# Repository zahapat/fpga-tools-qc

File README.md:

# CDL FPGA Environment for Quantum Computing

Welcome to the FPGA Environment for Quantum Computing template repository.

This repository is primarily designed for use with the [Xilinx Vivado Design Suite (HLx Edition build 2020.2)](https://www.xilinx.com/support/download/index.html/content/xilinx/en/downloadNav/vivado-design-tools/archive.html) on Windows platforms.

This repository contains VLSI hardware components, PCB layouts for Opal Kelly boards, and Vivado board files for high-speed data acquisition, clock synthesis, and other purposes within a quantum laboratory.

## Prerequisites

1. [Vivado Design Suite (HLx Edition build 2020.2)](https://www.xilinx.com/support/download/index.html/content/xilinx/en/downloadNav/vivado-design-tools/archive.html)
2. [ModelSim-Intel® FPGA Standard Edition, Version 20.1std](https://www.intel.com/content/www/us/en/software-kit/750637/modelsim-intel-fpgas-standard-edition-software-version-20-1.html?)
3. [Cygwin](https://www.cygwin.com/install.html) (GNU and Open Source tools for Linux-like functionality on Windows)
4. [App Installer (Winget)](https://apps.microsoft.com/store/detail/app-installer/9NBLGGH4NNS1) available on Microsoft Store.
5. Run all scripts in the directory `'./scripts/installers/win11/'` in the order 1 to 6 (plus the optional batch script afterwise) as an administrator to configure environment variables, install chocolate, Microsoft PowerShell, GitHub CLI (gh), and Make.
6. If you do not wish to install Python, comment the nineth line in the `'RunAsAdmin2-InstallEssentialAppsWin11.bat'`
7. After installing all the required software, go to the directory of this environment. Open this directory in your favourite terminal and run:
    ```shell
    make sim_init
    ```
    This will create a modelsim.ini file in the environment's root directory, necessary to launch simulations.

## Desctiption

The tools provided with this repository serve to offer tools and VLSI source files for facilitating the development of FPGA-based projects to build optimal and resource-efficient hardware.

One can find the following subdirectories:

1. Tcl

    `./tcl` contains Tcl scripts that interact with software supporting a Tcl (Tickle) console. They are designed for automating project building and running simulations using CLI (command-line interface).

2. Scripts

    The `'./scripts'` directory consists of the following tools:

   - Python-Notebook-Based FQEnv wrapper and control tool
   - The search for optimal MMCM (Mixed Mode Clock Manager) primitives analyzer for optimal clock synthesis
   - FIR Coefficients Generator
   - Generic parameters generator
   - Data Visualizer after successful readout

3. Modules

    The `./modules` directory serves as a repository of HDL modules created throughout the development. These modules consist of hardware description and Tcl scripts for adding files to Vivado Design Suite and Modelsim in correct compile order.

4. Boards

    This directory serves as a repository of Tcl-based generators of Vivado board `'*.bd'` files necessary to integrate the project cores with various AXI-based components. It is possible to inspect such bd file in Vivado IDE.

5. PCB

    The `'./pcb'` directory contains PCB design source files and gerber files to view, review, modify, or adapt PCB designs to new designs using KiCad. Gerber files can be directly sent to a PCB manufacturer.

6. Do

    The `'./do'` directory contains do scripts that enable launching and compiling source files within ModelSim.

7. Simulator

    The `'./simulator'` directory accompanies scripts in the `./do` directory. This is the output directory of the ModelSim simualtor. Also, it contains other basic do scripts to control simulation via the ModelSim Tcl command-line. Do scripts can be programmed using Tcl language.

8. Vivado

    This folder contains the Vivado project. While building the project, report files are being generated to inspect the properties of the hardware being generated, its resource utilization, timing, and more. These properties can also be inspected after launching the `*.xpr` Vivado project file located in this directory.

## Basic Functionality

The core unit of the FPGA Environment is the central Makefile located in the root direcotry of this repository. When opened in a text editor, it consists variables in upprecase and make targets which are named based on what one intends to do. For example, the `'make src'` target will add sources to Vivado; and `'make board'` will create and add the bd file to vivado. 

The following example reflects the main implementation flow. Run the following commands in your terminal after navigating to the root directory.

- Reset the environment:
    ```shell
    make reset
    ```

- Add all HDL sources under the given the relative Top file located in modules directory. In this case, the TOP variable defined in the Makefile will be explicitly updated by the desired source:
    ```shell
    make src TOP=fsm_gflow_tb.vhd
    ```

- To launch the simulation, type the following to the command line while being in the project root directory. This will launch ModelSim and start the simulation:
    ```shell
    make sim_gui
    ```

- To run hardware synthesis in out-of-context mode, run the following command:
    ```shell
    make ooc TOP=TOP=fsm_gflow.vhd
    ```

- To view the results in Vivado GUI mode, type the following to the CLI and wait until the project is open in Vivado:
    ```shell
    make gui
    ```

- Run all stages of implementation: synthesis, implementation, bitstream generation, hw platform generation (if applicable)
    ```shell
    make all
    ```

## Git: Create a New Repository

Update the `GIT_EMAIL` variable in `git.mk`. Use your email address to link Git with your Git account.
Run the following command to create a new private repo:

```shell
$ make git_new_private_repo
```

Run the following command to create a new public repository:

```shell
$ make git_new_public_repo
```

Run the following command to make the repository as a template:

```shell
$ make git_make_this_repo_template
```

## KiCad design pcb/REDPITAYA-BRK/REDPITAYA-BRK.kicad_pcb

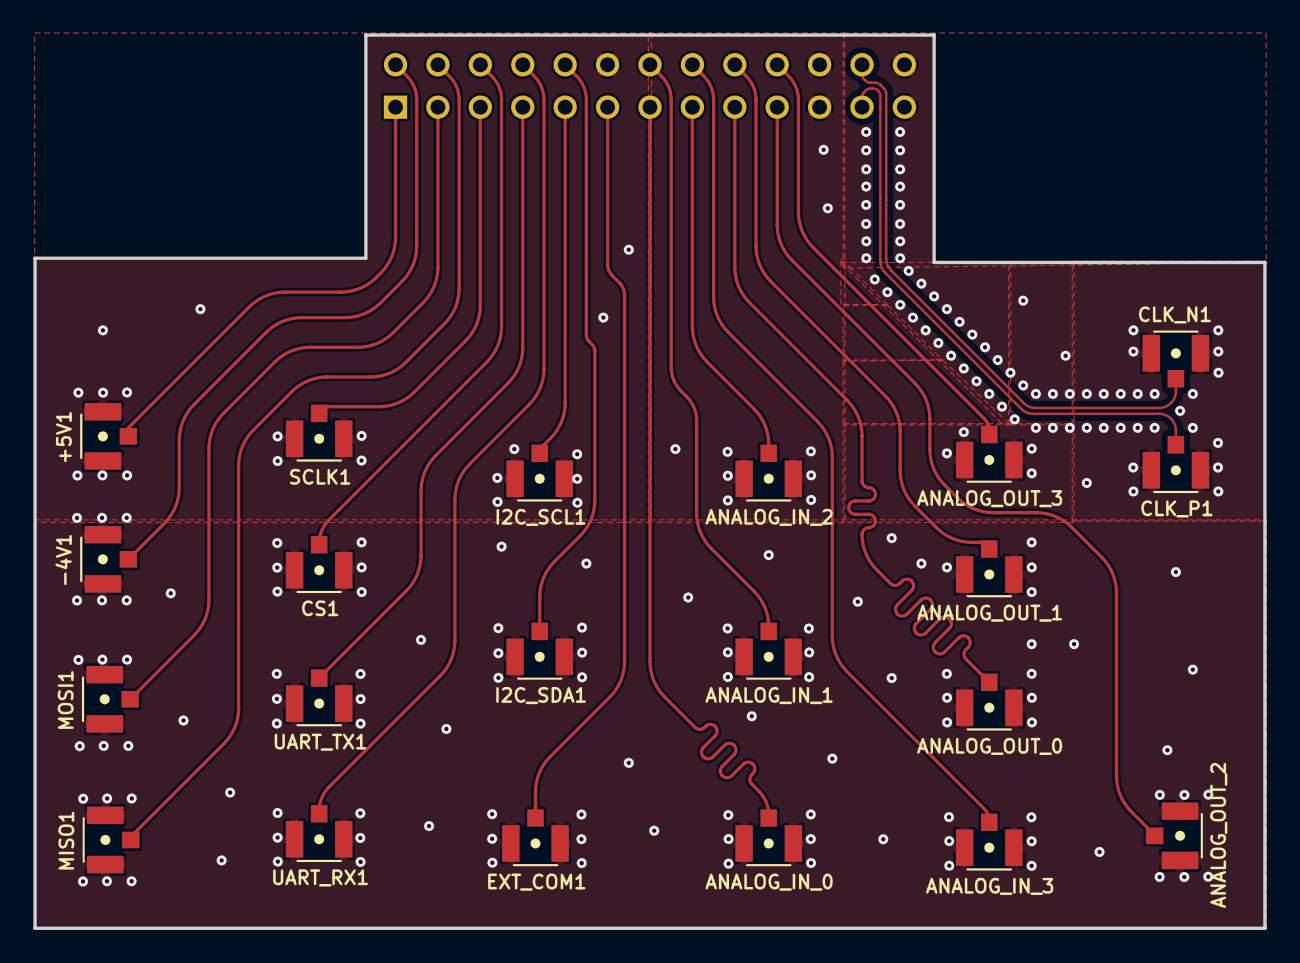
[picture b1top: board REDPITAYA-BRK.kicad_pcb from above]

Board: 4 copper layers, 73.7 x 53.5 mm, 22 parts (1 on the bottom side), 22 nets.

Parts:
+5V1: U.FL-R-SMT-1(10); HRS_U.FL-R-SMT-1(10)
-4V1: U.FL-R-SMT-1(10); HRS_U.FL-R-SMT-1(10)
ANALOG_IN_0, ANALOG_IN_1, ANALOG_IN_2, ANALOG_IN_3: U.FL-R-SMT-1(10); HRS_U.FL-R-SMT-1(10)
ANALOG_OUT_0, ANALOG_OUT_1, ANALOG_OUT_2, ANALOG_OUT_3: U.FL-R-SMT-1(10); HRS_U.FL-R-SMT-1(10)
CLK_N1: U.FL-R-SMT-1(10); HRS_U.FL-R-SMT-1(10)
CLK_P1: U.FL-R-SMT-1(10); HRS_U.FL-R-SMT-1(10)
CS1: U.FL-R-SMT-1(10); HRS_U.FL-R-SMT-1(10)
EXT_COM1: U.FL-R-SMT-1(10); HRS_U.FL-R-SMT-1(10)
I2C_SCL1, I2C_SDA1: U.FL-R-SMT-1(10); HRS_U.FL-R-SMT-1(10)
J1: 6-534206-3; TE_6-534206-3
MISO1: U.FL-R-SMT-1(10); HRS_U.FL-R-SMT-1(10)
MOSI1: U.FL-R-SMT-1(10); HRS_U.FL-R-SMT-1(10)
SCLK1: U.FL-R-SMT-1(10); HRS_U.FL-R-SMT-1(10)
UART_RX1: U.FL-R-SMT-1(10); HRS_U.FL-R-SMT-1(10)
UART_TX1: U.FL-R-SMT-1(10); HRS_U.FL-R-SMT-1(10)

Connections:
/CLK_N: CLK_N1.2 (SIG), J1.25
/CLK_P: CLK_P1.2 (SIG), J1.12
/ai0: ANALOG_IN_0.2 (SIG), J1.7
/ai1: ANALOG_IN_1.2 (SIG), J1.20
/ai2: ANALOG_IN_2.2 (SIG), J1.8
/ai3: ANALOG_IN_3.2 (SIG), J1.21
/ao0: ANALOG_OUT_0.2 (SIG), J1.9
/ao1: ANALOG_OUT_1.2 (SIG), J1.22
/ao2: ANALOG_OUT_2.2 (SIG), J1.10
/ao3: ANALOG_OUT_3.2 (SIG), J1.23
/cs: CS1.2 (SIG), J1.16
/ext_com: EXT_COM1.2 (SIG), J1.6
/i2c_scl: I2C_SCL1.2 (SIG), J1.5
/i2c_sda: I2C_SDA1.2 (SIG), J1.18
/m4v: -4V1.2 (SIG), J1.14
/miso: J1.15, MISO1.2 (SIG)
/mosi: J1.2, MOSI1.2 (SIG)
/p5v: +5V1.2 (SIG), J1.1
/sclk: J1.3, SCLK1.2 (SIG)
/uart_rx: J1.17, UART_RX1.2 (SIG)
/uart_tx: J1.4, UART_TX1.2 (SIG)
GND: +5V1.1 (GND), +5V1.3 (GND), -4V1.1 (GND), -4V1.3 (GND), ANALOG_IN_0.1 (GND), ANALOG_IN_0.3 (GND), ANALOG_IN_1.1 (GND), ANALOG_IN_1.3 (GND), ANALOG_IN_2.1 (GND), ANALOG_IN_2.3 (GND), ANALOG_IN_3.1 (GND), ANALOG_IN_3.3 (GND), ANALOG_OUT_0.1 (GND), ANALOG_OUT_0.3 (GND), ANALOG_OUT_1.1 (GND), ANALOG_OUT_1.3 (GND), ANALOG_OUT_2.1 (GND), ANALOG_OUT_2.3 (GND), ANALOG_OUT_3.1 (GND), ANALOG_OUT_3.3 (GND), CLK_N1.1 (GND), CLK_N1.3 (GND), CLK_P1.1 (GND), CLK_P1.3 (GND), CS1.1 (GND), CS1.3 (GND), EXT_COM1.1 (GND), EXT_COM1.3 (GND), I2C_SCL1.1 (GND), I2C_SCL1.3 (GND), I2C_SDA1.1 (GND), I2C_SDA1.3 (GND), J1.11, J1.13, J1.19, J1.24, J1.26, MISO1.1 (GND), MISO1.3 (GND), MOSI1.1 (GND), MOSI1.3 (GND), SCLK1.1 (GND), SCLK1.3 (GND), UART_RX1.1 (GND), UART_RX1.3 (GND), UART_TX1.1 (GND), UART_TX1.3 (GND)

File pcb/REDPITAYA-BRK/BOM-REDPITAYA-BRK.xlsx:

|  |  | xxxx xxxx xxxxx xxPCS BOM (Sample Bill of Materials)
Item # | *Designator | *Qty | Manufacturer | *Mfg Part # | Description / Value | *Package/Footprint | Type | Your Instructions / Notes
1 | ANALOG_OUT_1 | 1 | Hirose Electric Co Ltd | U.FL-R-SMT-1(10) | U.FL (UMCC) Connector Receptacle, Male Pin 50Ohm Surface Mount Solder | HRS_U.FL-R-SMT-1(10) | SMD | Datasheet: https://media.digikey.com/pdf/Data%20Sheets/Hirose%20PDFs/ED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
2 | +5V1 | 1 | Hirose Electric Co Ltd | U.FL-R-SMT-1(10) | U.FL (UMCC) Connector Receptacle, Male Pin 50Ohm Surface Mount Solder | HRS_U.FL-R-SMT-1(10) | SMD | Datasheet: https://media.digikey.com/pdf/Data%20Sheets/Hirose%20PDFs/ED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
3 | I2C_SDA1 | 1 | Hirose Electric Co Ltd | U.FL-R-SMT-1(10) | U.FL (UMCC) Connector Receptacle, Male Pin 50Ohm Surface Mount Solder | HRS_U.FL-R-SMT-1(10) | SMD | Datasheet: https://media.digikey.com/pdf/Data%20Sheets/Hirose%20PDFs/ED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
4 | ANALOG_IN_3 | 1 | Hirose Electric Co Ltd | U.FL-R-SMT-1(10) | U.FL (UMCC) Connector Receptacle, Male Pin 50Ohm Surface Mount Solder | HRS_U.FL-R-SMT-1(10) | SMD | Datasheet: https://media.digikey.com/pdf/Data%20Sheets/Hirose%20PDFs/ED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
5 | -4V1 | 1 | Hirose Electric Co Ltd | U.FL-R-SMT-1(10) | U.FL (UMCC) Connector Receptacle, Male Pin 50Ohm Surface Mount Solder | HRS_U.FL-R-SMT-1(10) | SMD | Datasheet: https://media.digikey.com/pdf/Data%20Sheets/Hirose%20PDFs/ED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
6 | UART_RX1 | 1 | Hirose Electric Co Ltd | U.FL-R-SMT-1(10) | U.FL (UMCC) Connector Receptacle, Male Pin 50Ohm Surface Mount Solder | HRS_U.FL-R-SMT-1(10) | SMD | Datasheet: https://media.digikey.com/pdf/Data%20Sheets/Hirose%20PDFs/ED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
7 | ANALOG_IN_0 | 1 | Hirose Electric Co Ltd | U.FL-R-SMT-1(10) | U.FL (UMCC) Connector Receptacle, Male Pin 50Ohm Surface Mount Solder | HRS_U.FL-R-SMT-1(10) | SMD | Datasheet: https://media.digikey.com/pdf/Data%20Sheets/Hirose%20PDFs/ED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
8 | UART_TX1 | 1 | Hirose Electric Co Ltd | U.FL-R-SMT-1(10) | U.FL (UMCC) Connector Receptacle, Male Pin 50Ohm Surface Mount Solder | HRS_U.FL-R-SMT-1(10) | SMD | Datasheet: https://media.digikey.com/pdf/Data%20Sheets/Hirose%20PDFs/ED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
9 | EXT_COM1 | 1 | Hirose Electric Co Ltd | U.FL-R-SMT-1(10) | U.FL (UMCC) Connector Receptacle, Male Pin 50Ohm Surface Mount Solder | HRS_U.FL-R-SMT-1(10) | SMD | Datasheet: https://media.digikey.com/pdf/Data%20Sheets/Hirose%20PDFs/ED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
10 | MOSI1 | 1 | Hirose Electric Co Ltd | U.FL-R-SMT-1(10) | U.FL (UMCC) Connector Receptacle, Male Pin 50Ohm Surface Mount Solder | HRS_U.FL-R-SMT-1(10) | SMD | Datasheet: https://media.digikey.com/pdf/Data%20Sheets/Hirose%20PDFs/ED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
11 | ANALOG_IN_1 | 1 | Hirose Electric Co Ltd | U.FL-R-SMT-1(10) | U.FL (UMCC) Connector Receptacle, Male Pin 50Ohm Surface Mount Solder | HRS_U.FL-R-SMT-1(10) | SMD | Datasheet: https://media.digikey.com/pdf/Data%20Sheets/Hirose%20PDFs/ED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
12 | ANALOG_IN_2 | 1 | Hirose Electric Co Ltd | U.FL-R-SMT-1(10) | U.FL (UMCC) Connector Receptacle, Male Pin 50Ohm Surface Mount Solder | HRS_U.FL-R-SMT-1(10) | SMD | Datasheet: https://media.digikey.com/pdf/Data%20Sheets/Hirose%20PDFs/ED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
13 | CLK_N1 | 1 | Hirose Electric Co Ltd | U.FL-R-SMT-1(10) | U.FL (UMCC) Connector Receptacle, Male Pin 50Ohm Surface Mount Solder | HRS_U.FL-R-SMT-1(10) | SMD | Datasheet: https://media.digikey.com/pdf/Data%20Sheets/Hirose%20PDFs/ED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
14 | ANALOG_OUT_2 | 1 | Hirose Electric Co Ltd | U.FL-R-SMT-1(10) | U.FL (UMCC) Connector Receptacle, Male Pin 50Ohm Surface Mount Solder | HRS_U.FL-R-SMT-1(10) | SMD | Datasheet: https://media.digikey.com/pdf/Data%20Sheets/Hirose%20PDFs/ED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
15 | ANALOG_OUT_0 | 1 | Hirose Electric Co Ltd | U.FL-R-SMT-1(10) | U.FL (UMCC) Connector Receptacle, Male Pin 50Ohm Surface Mount Solder | HRS_U.FL-R-SMT-1(10) | SMD | Datasheet: https://media.digikey.com/pdf/Data%20Sheets/Hirose%20PDFs/ED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
16 | MISO1 | 1 | Hirose Electric Co Ltd | U.FL-R-SMT-1(10) | U.FL (UMCC) Connector Receptacle, Male Pin 50Ohm Surface Mount Solder | HRS_U.FL-R-SMT-1(10) | SMD | Datasheet: https://media.digikey.com/pdf/Data%20Sheets/Hirose%20PDFs/ED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
17 | ANALOG_OUT_3 | 1 | Hirose Electric Co Ltd | U.FL-R-SMT-1(10) | U.FL (UMCC) Connector Receptacle, Male Pin 50Ohm Surface Mount Solder | HRS_U.FL-R-SMT-1(10) | SMD | Datasheet: https://media.digikey.com/pdf/Data%20Sheets/Hirose%20PDFs/ED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
18 | CLK_P1 | 1 | Hirose Electric Co Ltd | U.FL-R-SMT-1(10) | U.FL (UMCC) Connector Receptacle, Male Pin 50Ohm Surface Mount Solder | HRS_U.FL-R-SMT-1(10) | SMD | Datasheet: https://media.digikey.com/pdf/Data%20Sheets/Hirose%20PDFs/ED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
19 | SCLK1 | 1 | Hirose Electric Co Ltd | U.FL-R-SMT-1(10) | U.FL (UMCC) Connector Receptacle, Male Pin 50Ohm Surface Mount Solder | HRS_U.FL-R-SMT-1(10) | SMD | Datasheet: https://media.digikey.com/pdf/Data%20Sheets/Hirose%20PDFs/ED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
20 | I2C_SCL1 | 1 | Hirose Electric Co Ltd | U.FL-R-SMT-1(10) | U.FL (UMCC) Connector Receptacle, Male Pin 50Ohm Surface Mount Solder | HRS_U.FL-R-SMT-1(10) | SMD | Datasheet: https://media.digikey.com/pdf/Data%20Sheets/Hirose%20PDFs/ED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
21 | CS1 | 1 | Hirose Electric Co Ltd | U.FL-R-SMT-1(10) | U.FL (UMCC) Connector Receptacle, Male Pin 50Ohm Surface Mount Solder | HRS_U.FL-R-SMT-1(10) | SMD | Datasheet: https://media.digikey.com/pdf/Data%20Sheets/Hirose%20PDFs/ED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
22 | J1 | 1 | TE Connectivity AMP Connectors | 6-534206-3 | 26 Position Receptacle Connector 0.100" (2.54mm) Through Hole Gold | TE_6-534206-3 | SMD | Datasheet: https://www.te.com/commerce/DocumentDelivery/DDEController?A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

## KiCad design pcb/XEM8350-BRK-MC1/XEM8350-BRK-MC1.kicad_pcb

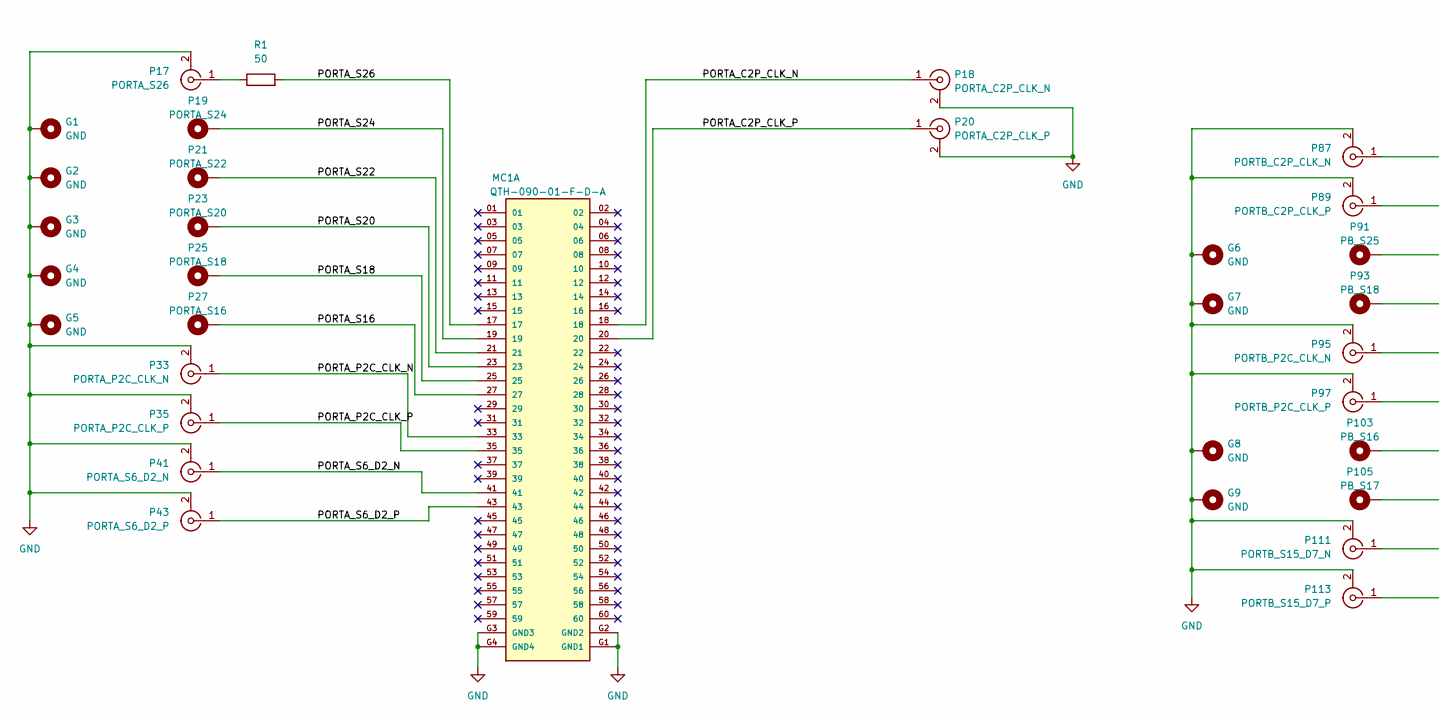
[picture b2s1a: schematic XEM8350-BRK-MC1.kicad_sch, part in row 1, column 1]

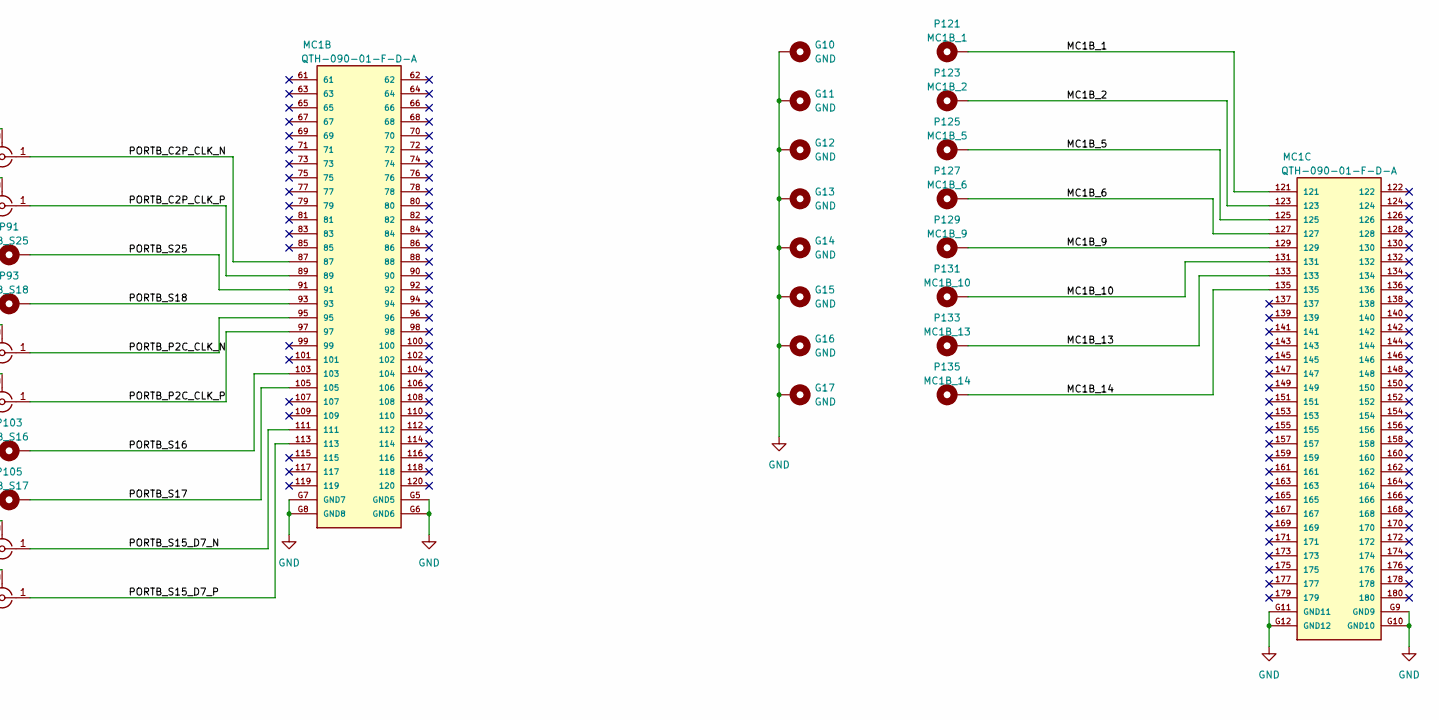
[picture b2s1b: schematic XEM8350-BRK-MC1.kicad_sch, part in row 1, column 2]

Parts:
G1, G2, G3, G4, G5, G6, G7, G8, G9, G10, G11, G12, G13, G14, G15, G16, G17: GND; Custom_Signal_Hole_Pad-001
MC1: QTH-090-01-F-D-A; SAMTEC_QTH-090-01-X-D-A; PARTREV L
P17: PORTA_S26; SMA_Amphenol_901-144_Vertical
P18: PORTA_C2P_CLK_N; SMA_Amphenol_901-144_Vertical
P19: PORTA_S24; Custom_Signal_Hole_Pad-001
P20: PORTA_C2P_CLK_P; SMA_Amphenol_901-144_Vertical
P21: PORTA_S22; Custom_Signal_Hole_Pad-001
P23: PORTA_S20; Custom_Signal_Hole_Pad-001
P25: PORTA_S18; Custom_Signal_Hole_Pad-001
P27: PORTA_S16; Custom_Signal_Hole_Pad-001
P33: PORTA_P2C_CLK_N; SMA_Amphenol_901-144_Vertical
P35: PORTA_P2C_CLK_P; SMA_Amphenol_901-144_Vertical
P41: PORTA_S6_D2_N; SMA_Amphenol_901-144_Vertical
P43: PORTA_S6_D2_P; SMA_Amphenol_901-144_Vertical
P87: PORTB_C2P_CLK_N; SMA_Amphenol_901-144_Vertical
P89: PORTB_C2P_CLK_P; SMA_Amphenol_901-144_Vertical
P91: PB_S25; Custom_Signal_Hole_Pad-001
P93: PB_S18; Custom_Signal_Hole_Pad-001
P95: PORTB_P2C_CLK_N; SMA_Amphenol_901-144_Vertical
P97: PORTB_P2C_CLK_P; SMA_Amphenol_901-144_Vertical
P103: PB_S16; Custom_Signal_Hole_Pad-001
P105: PB_S17; Custom_Signal_Hole_Pad-001
P111: PORTB_S15_D7_N; SMA_Amphenol_901-144_Vertical
P113: PORTB_S15_D7_P; SMA_Amphenol_901-144_Vertical
P121: MC1B_1; Custom_Signal_Hole_Pad-001
P123: MC1B_2; Custom_Signal_Hole_Pad-001
P125: MC1B_5; Custom_Signal_Hole_Pad-001
P127: MC1B_6; Custom_Signal_Hole_Pad-001
P129: MC1B_9; Custom_Signal_Hole_Pad-001
P131: MC1B_10; Custom_Signal_Hole_Pad-001
P133: MC1B_13; Custom_Signal_Hole_Pad-001
P135: MC1B_14; Custom_Signal_Hole_Pad-001
R1: 50; RESC1608X59N

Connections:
/MC1B_1: MC1.121, P121.1
/MC1B_2: MC1.123, P123.1
/MC1B_5: MC1.125, P125.1
/MC1B_6: MC1.127, P127.1
/MC1B_9: MC1.129, P129.1
/MC1B_10: MC1.131, P131.1
/MC1B_13: MC1.133, P133.1
/MC1B_14: MC1.135, P135.1
/PORTA_C2P_CLK_N: MC1.18, P18.1 (In)
/PORTA_C2P_CLK_P: MC1.20, P20.1 (In)
/PORTA_P2C_CLK_N: MC1.33, P33.1 (In)
/PORTA_P2C_CLK_P: MC1.35, P35.1 (In)
/PORTA_S6_D2_N: MC1.41, P41.1 (In)
/PORTA_S6_D2_P: MC1.43, P43.1 (In)
/PORTA_S16: MC1.27, P27.1
/PORTA_S18: MC1.25, P25.1
/PORTA_S20: MC1.23, P23.1
/PORTA_S22: MC1.21, P21.1
/PORTA_S24: MC1.19, P19.1
/PORTA_S26: MC1.17, R1.2
/PORTB_C2P_CLK_N: MC1.87, P87.1 (In)
/PORTB_C2P_CLK_P: MC1.89, P89.1 (In)
/PORTB_P2C_CLK_N: MC1.95, P95.1 (In)
/PORTB_P2C_CLK_P: MC1.97, P97.1 (In)
/PORTB_S15_D7_N: MC1.111, P111.1 (In)
/PORTB_S15_D7_P: MC1.113, P113.1 (In)
/PORTB_S16: MC1.103, P103.1
/PORTB_S17: MC1.105, P105.1
/PORTB_S18: MC1.93, P93.1
/PORTB_S25: MC1.91, P91.1
GND: G1.1, G2.1, G3.1, G4.1, G5.1, G6.1, G7.1, G8.1, G9.1, G10.1, G11.1, G12.1, G13.1, G14.1, G15.1, G16.1, G17.1, MC1.G1 (GND1), MC1.G2 (GND2), MC1.G3 (GND3), MC1.G4 (GND4), MC1.G5 (GND5), MC1.G6 (GND6), MC1.G7 (GND7), MC1.G8 (GND8), MC1.G9 (GND9), MC1.G10 (GND10), MC1.G11 (GND11), MC1.G12 (GND12), P17.2 (Ext), P18.2 (Ext), P20.2 (Ext), P33.2 (Ext), P35.2 (Ext), P41.2 (Ext), P43.2 (Ext), P87.2 (Ext), P89.2 (Ext), P95.2 (Ext), P97.2 (Ext), P111.2 (Ext), P113.2 (Ext)
unnamed: P17.1 (In), R1.1

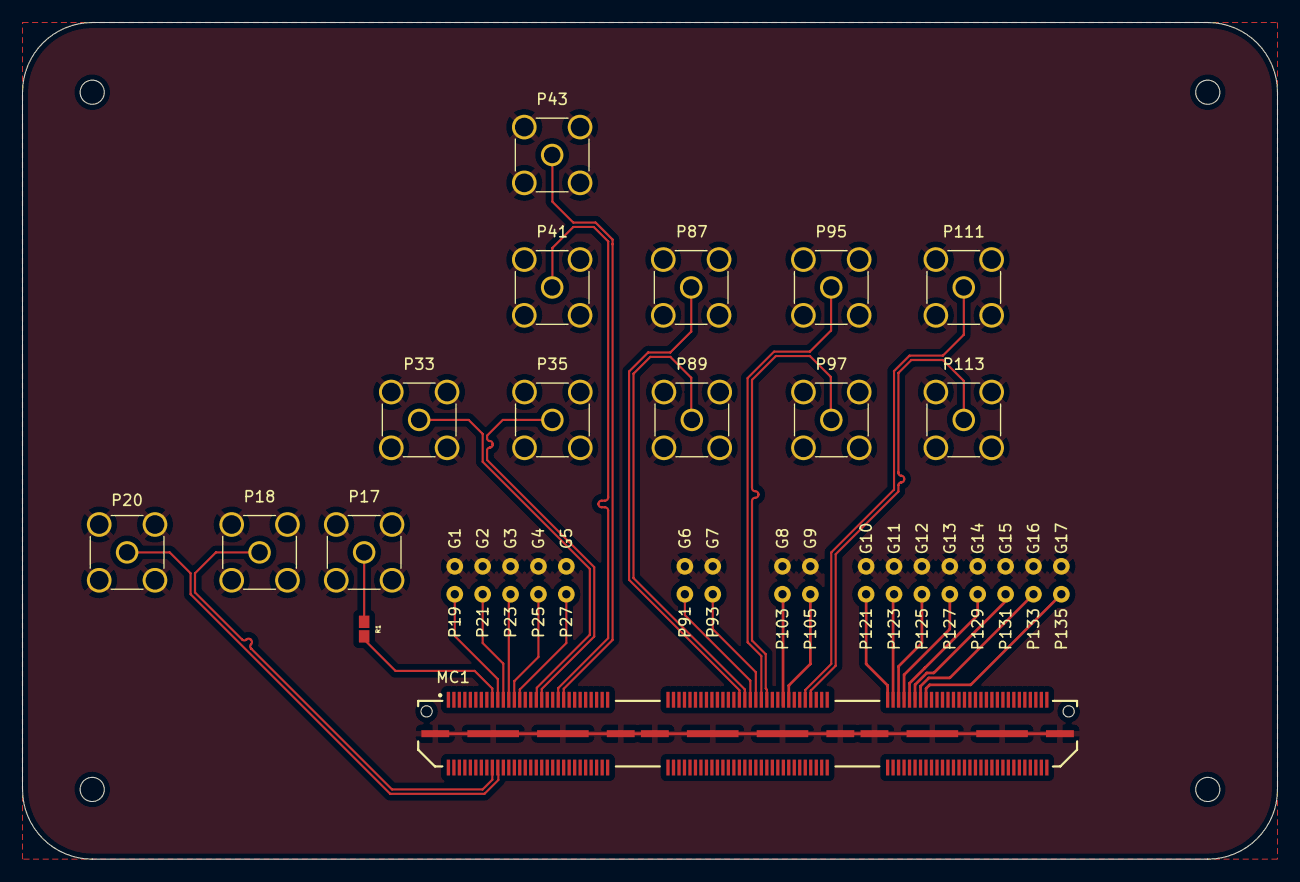
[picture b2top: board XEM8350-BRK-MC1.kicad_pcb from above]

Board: 2 copper layers, 114.3 x 76.2 mm, 49 parts (0 on the bottom side), 32 nets.

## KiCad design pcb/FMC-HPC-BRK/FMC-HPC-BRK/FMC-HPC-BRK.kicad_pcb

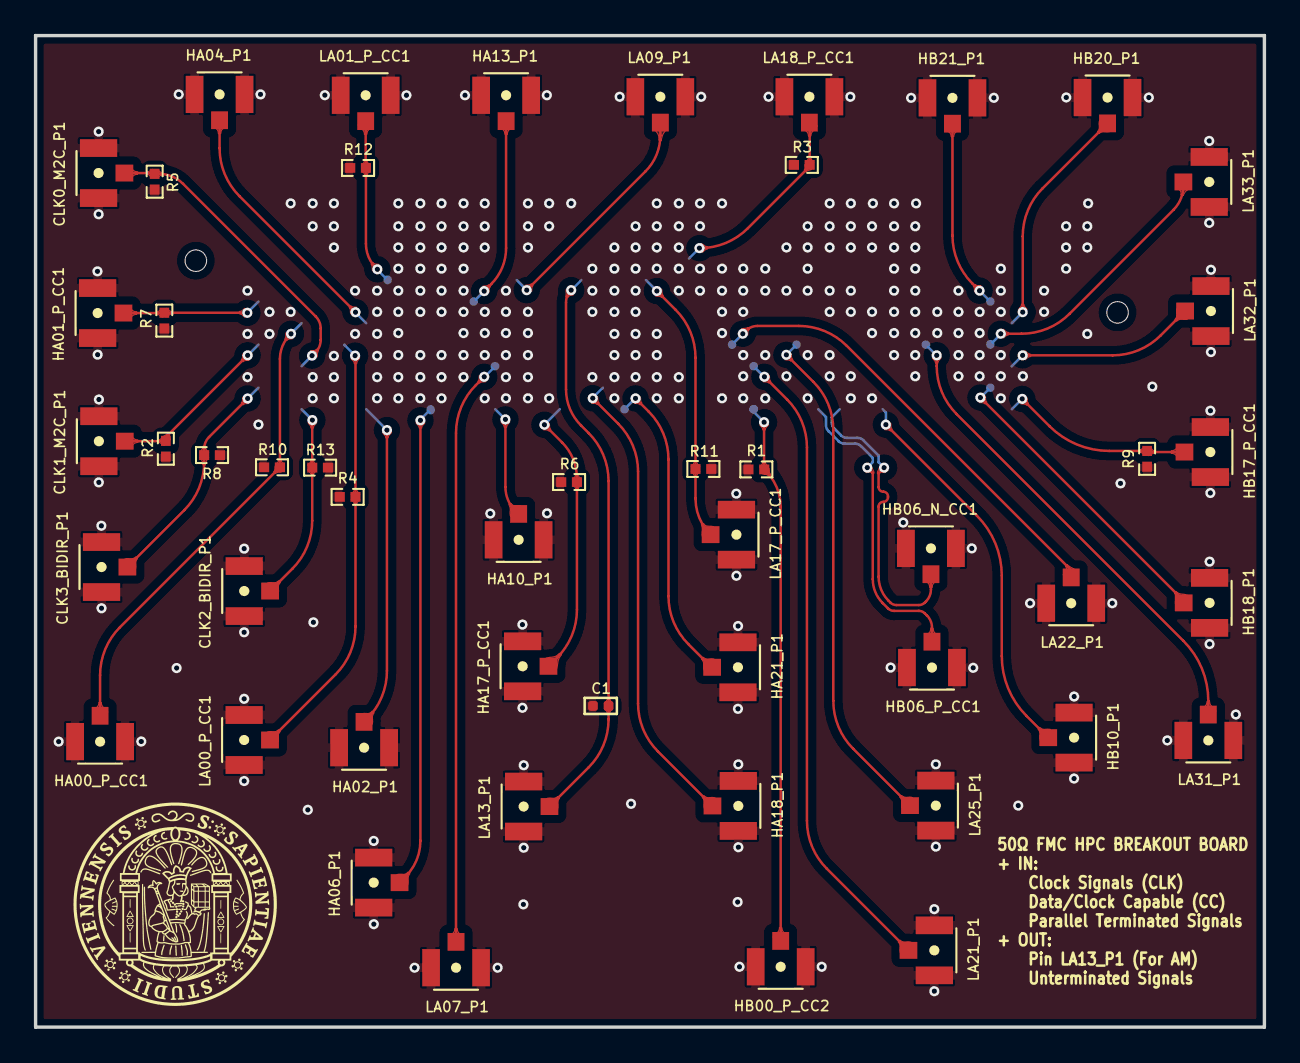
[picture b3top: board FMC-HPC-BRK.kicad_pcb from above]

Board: 4 copper layers, 72.5 x 58.5 mm, 50 parts (1 on the bottom side), 36 nets.

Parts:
C1: CAP; CAPC100X50X55L25N
CLK0_M2C_P1, CLK1_M2C_P1, CLK2_BIDIR_P1, CLK3_BIDIR_P1: U.FL-R-SMT-1(10); HRS_U.FL-R-SMT-1(10)
HA00_P_CC1, HA01_P_CC1, HA02_P1, HA04_P1, HA06_P1, HA10_P1, HA13_P1, HA17_P_CC1, HA18_P1, HA21_P1: U.FL-R-SMT-1(10); HRS_U.FL-R-SMT-1(10)
HB00_P_CC2, HB06_N_CC1, HB06_P_CC1, HB10_P1, HB17_P_CC1, HB18_P1, HB20_P1, HB21_P1: U.FL-R-SMT-1(10); HRS_U.FL-R-SMT-1(10)
J1: ASP-134488-01; SAMTEC_ASP-134488-01
LA00_P_CC1, LA01_P_CC1, LA07_P1, LA09_P1, LA13_P1, LA17_P_CC1, LA18_P_CC1, LA21_P1, LA22_P1, LA25_P1, LA31_P1, LA32_P1, LA33_P1: U.FL-R-SMT-1(10); HRS_U.FL-R-SMT-1(10)
R1, R2, R3, R4, R5, R6, R7, R8, R9, R10, R11, R12, R13: R; RESC100X50X35L25

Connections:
/B8b: J1.G33, LA01_P_CC1.2 (SIG), R12.2
/B14b: J1.G27, LA09_P1.2 (SIG)
/B17b: C1.2, J1.G24, LA13_P1.2 (SIG)
/B20b: J1.G21, LA17_P_CC1.2 (SIG), R11.2
/B22a: J1.H19, LA18_P_CC1.2 (SIG), R3.2
/C2a: HA01_P_CC1.2 (SIG), J1.F39, R7.2
/C4b: HA00_P_CC1.2 (SIG), J1.E37, R10.2
/C7b: HA04_P1.2 (SIG), J1.E34
/C12a: HA13_P1.2 (SIG), J1.F29
/C36a: HB21_P1.2 (SIG), J1.F5
/C37b: HB20_P1.2 (SIG), J1.E4
/D2a: CLK1_M2C_P1.2 (SIG), J1.D39, R2.2
/D4b: CLK0_M2C_P1.2 (SIG), J1.C37, R5.2
/D6a: J1.D35, LA00_P_CC1.2 (SIG), R4.2
/D13b: J1.C28, LA07_P1.2 (SIG)
/D24a: J1.D17, LA22_P1.2 (SIG)
/D25b: J1.C16, LA21_P1.2 (SIG)
/D27a: J1.D14, LA25_P1.2 (SIG)
/D33a: J1.D8, LA31_P1.2 (SIG)
/D36a: J1.D5, LA33_P1.2 (SIG)
/D37b: J1.C4, LA32_P1.2 (SIG)
/E2a: CLK3_BIDIR_P1.2 (SIG), J1.B39, R8.2
/E4b: CLK2_BIDIR_P1.2 (SIG), J1.A37, R13.2
/E7b: HA02_P1.2 (SIG), J1.A34
/E10b: HA06_P1.2 (SIG), J1.A31
/E13b: HA10_P1.2 (SIG), J1.A28
/E16b: HA17_P_CC1.2 (SIG), J1.A25, R6.2
/E18a: HA18_P1.2 (SIG), J1.B23
/E19b: HA21_P1.2 (SIG), J1.A22
/E25b: HB00_P_CC2.2 (SIG), J1.A16, R1.2
/E28b_N: HB06_N_CC1.2 (SIG), J1.A12
/E28b_P: HB06_P_CC1.2 (SIG), J1.A13
/E31b_P: HB10_P1.2 (SIG), J1.A10
/E36a: HB18_P1.2 (SIG), J1.B5
/E37b: HB17_P_CC1.2 (SIG), J1.A4, R9.2
GND: C1.1, CLK0_M2C_P1.1 (GND), CLK0_M2C_P1.3 (GND), CLK1_M2C_P1.1 (GND), CLK1_M2C_P1.3 (GND), CLK2_BIDIR_P1.1 (GND), CLK2_BIDIR_P1.3 (GND), CLK3_BIDIR_P1.1 (GND), CLK3_BIDIR_P1.3 (GND), HA00_P_CC1.1 (GND), HA00_P_CC1.3 (GND), HA01_P_CC1.1 (GND), HA01_P_CC1.3 (GND), HA02_P1.1 (GND), HA02_P1.3 (GND), HA04_P1.1 (GND), HA04_P1.3 (GND), HA06_P1.1 (GND), HA06_P1.3 (GND), HA10_P1.1 (GND), HA10_P1.3 (GND), HA13_P1.1 (GND), HA13_P1.3 (GND), HA17_P_CC1.1 (GND), HA17_P_CC1.3 (GND), HA18_P1.1 (GND), HA18_P1.3 (GND), HA21_P1.1 (GND), HA21_P1.3 (GND), HB00_P_CC2.1 (GND), HB00_P_CC2.3 (GND), HB06_N_CC1.1 (GND), HB06_N_CC1.3 (GND), HB06_P_CC1.1 (GND), HB06_P_CC1.3 (GND), HB10_P1.1 (GND), HB10_P1.3 (GND), HB17_P_CC1.1 (GND), HB17_P_CC1.3 (GND), HB18_P1.1 (GND), HB18_P1.3 (GND), HB20_P1.1 (GND), HB20_P1.3 (GND), HB21_P1.1 (GND), HB21_P1.3 (GND), J1.A2, J1.A5, J1.A8, J1.A11, J1.A14, J1.A17, J1.A20, J1.A23, J1.A26, J1.A29, J1.A32, J1.A35, J1.A38, J1.A39, J1.B1, J1.B3, J1.B6, J1.B9, J1.B12, J1.B15, J1.B18, J1.B21, J1.B24, J1.B27, J1.B30, J1.B33, J1.B36, J1.B37, J1.B40, J1.C2, J1.C5, J1.C8, J1.C11, J1.C14, J1.C17, J1.C20, J1.C23, J1.C26, J1.C29, J1.C32, J1.C35, J1.C38, J1.D1, J1.D3, J1.D6, J1.D9, J1.D12, J1.D15, J1.D18, J1.D21, J1.D24, J1.D27, J1.D30, J1.D33, J1.D36, J1.D37, J1.D40, J1.E2, J1.E5, J1.E8, J1.E11, J1.E14, J1.E17, J1.E20, J1.E23, J1.E26, J1.E29, J1.E32, J1.E35, J1.E38, J1.E39, J1.F1, J1.F3, J1.F6, J1.F9, J1.F12, J1.F15, J1.F18, J1.F21, J1.F24, J1.F27, J1.F30, J1.F33, J1.F36, J1.F37, J1.F40, J1.G2, J1.G4, J1.G13, J1.G16, J1.G19, J1.G22, J1.G25, J1.G28, J1.G31, J1.G34, J1.G35, J1.G38, J1.G39, J1.H1, J1.H3, J1.H5, J1.H8, J1.H9, J1.H12, J1.H13, J1.H16, J1.H17, J1.H20, J1.H21, J1.H24, J1.H25, J1.H28, J1.H29, J1.H32, J1.H33, J1.H36, J1.H37, J1.H40, J1.J2, J1.J3, J1.J6, J1.J7, J1.J10, J1.J11, J1.J14, J1.J15, J1.J18, J1.J19, J1.J22, J1.J23, J1.J26, J1.J27, J1.J30, J1.J31, J1.J34, J1.J35, J1.J38, J1.J39, J1.K1, J1.K4, J1.K5, J1.K8, J1.K9, J1.K12, J1.K13, J1.K16, J1.K17, J1.K20, J1.K21, J1.K24, J1.K25, J1.K28, J1.K29, J1.K32, J1.K33, J1.K36, J1.K37, J1.K40, LA00_P_CC1.1 (GND), LA00_P_CC1.3 (GND), LA01_P_CC1.1 (GND), LA01_P_CC1.3 (GND), LA07_P1.1 (GND), LA07_P1.3 (GND), LA09_P1.1 (GND), LA09_P1.3 (GND), LA13_P1.1 (GND), LA13_P1.3 (GND), LA17_P_CC1.1 (GND), LA17_P_CC1.3 (GND), LA18_P_CC1.1 (GND), LA18_P_CC1.3 (GND), LA21_P1.1 (GND), LA21_P1.3 (GND), LA22_P1.1 (GND), LA22_P1.3 (GND), LA25_P1.1 (GND), LA25_P1.3 (GND), LA31_P1.1 (GND), LA31_P1.3 (GND), LA32_P1.1 (GND), LA32_P1.3 (GND), LA33_P1.1 (GND), LA33_P1.3 (GND), R1.1, R2.1, R3.1, R4.1, R5.1, R6.1, R7.1, R8.1, R9.1, R10.1, R11.1, R12.1, R13.1

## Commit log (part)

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2022-09-15 fix: Change old GIT_TEMPLATE variable to newly created template
2022-09-15 feat: Add project specific makefile targets to project_specific.mk
2022-09-15 feat: Add links to new targets in project_specific.mk in Makefile
2022-09-15 feat: Add new Redis make commands
2022-09-15 feat: Create new project initialization generic make targets
2022-09-15 feat: Create new UVVM generator make target
2022-09-15 feat: Create new generic GUI make commands
2022-09-15 feat: Create new make commands for CRC generator
2022-09-15 feat: Create new make commands for Vitis
2022-09-15 feat: Create new make commands for Vivado
2022-09-15 feat: Create new make commands for Modelsim
2022-09-15 doc: Add LICENSE.txt
2022-09-16 doc: Correct indentation
2022-09-16 feat: Add generic and project-specific make variables
2022-09-16 feat: Add TOP make variable for make src
2022-09-16 feat: Add Tcl scripts and adapt paths in makefiles
2022-09-16 fix: Move make_generics.tcl to project_specific directory
2022-09-16 fix: Change target folder for pushing changes to template repo
2022-09-16 feat: Add gitignore
2022-11-10 feat: Add scripts and adapt changes in makefile
    feat: Add scripts and adapt changes in makefile
2022-11-10 fix: Change output directory for make_generics.tcl generation
2022-11-10 doc: Update README.md in tcl
2022-11-10 fix: Remove useless targets
2022-11-10 doc: Create README.md in tcl
2022-11-10 feat: Add HDL modules
2022-11-10 feat: Add modelsim directory without precompiled libraries
2022-11-10 fix: Move make reset command to vivado.mk
2022-11-10 fix: Switch to branch after set remote
2022-11-10 feat: Create update targets to makefile
2022-11-10 feat: Add packages dir and update environment
2022-11-10 feat: Add .do and .tcl files for modelsim
2022-11-10 fix: Replace cloning new private repo by fetch and merge changes
2022-11-10 doc: Add test description to README.md in tcl
2022-11-10 fix: Set remote url before checkout to main in new repo
2022-11-10 fix: Rename git update repo make commands
2022-11-10 doc: Add comments to git.mk
2022-11-10 feat: Add make target to update local files from template remote
2022-11-10 refactor: Remove unused update make targets in git.mk
2022-11-10 refactor: Get history for new repos from template
2022-11-10 fix: Go back to current default branch after update templrepo
2022-11-10 fix: Change fetch command by pull with unrelated histories
2022-11-10 refactor: Remove redundant subshell environment
2022-11-10 fix: Change output dir from tcl to project specific in generics make cmd
2022-11-10 feat: Create new build proj specific make command
    feat: Create new build proj specific make command
2022-11-10 fix: Install pip in elevated mode
2022-11-10 feat: Support new commands in the top make file
    feat: Support new commands in the top make file
2022-11-10 fix: Clean temporary files from vivado engine with new and clean make commands
2022-11-10 fix: Remove make generics from build cmd
    fix: Remove make generics from build cmd
2022-11-10 fix: Remove make command requirements for simulators in Makefile
2022-11-10 fix: Move make variables form top to vivado make subfile
    fix: Move make variables form top to vivado make subfile
2022-11-10 fix: Remove upgrade buildtools from make winget_upgrade
2022-11-10 fix: Remove faulty make command requirements for commands in Makefile
2022-11-10 fix: Upgrade pip in elevated mode
2022-11-10 fix: Remove quotes from arguments passed to vivado make commands
2022-11-10 fix: Remove install windows software in packages.mk
2022-11-10 fix: Remove faulty make command requirement in Makefile
2022-11-10 refactor: Improve readability of the code
    refactor: Improve readability of the code
2022-11-10 fix: Prevent adding files already existing in the project
    fix: Prevent adding files already existing in the project
2022-11-10 refactor: Rename proj specific make files for better readability
2022-11-10 fix: Remove force flag in git add to template
2022-11-10 feat: Prevent searching in redundant directories in make src
2022-11-10 fix: Remove output file for gitignore
2022-11-10 feat: Delete .str vivado files in new and clean make commands
2022-11-10 refactor: Remove IP product files
2022-11-10 feat: Add run_all tcl script
    feat: Add run_all tcl script
2022-11-10 fix: Correct OK input port constants in gflow_top
2022-11-10 fix: Correct only pushing live changes to project only
2022-11-10 fix: Rename generic in top file to match src
2022-11-10 fix: Prevent HW platform generation when Vitis modules not available in the design
2022-11-10 fix: Remove quit break in run_all
2022-11-10 fix: Reduce verbosity and reuse code in build make cmd
2022-11-10 feat: Add default target section in Makefile
2022-11-10 fix: Converted path to compile_order file to normalized
2022-11-10 refactor: Add explicit paths in prerequisites to reduce complexity
2022-11-10 fix: Correct location of output bitfiles as recipe for reset_bitfiles
2022-11-10 feat: Enable adding a specific board file to project
    feat: Enable adding a specific board file to project
    feat: Enable adding a specific board file to project
2022-11-10 fix: Correct trimming incorrect part of normalized path
    fix: Correct trimming incorrect part of normalized path
2022-11-10 fix: Remove board files from git
    fix: Remove board files from git
2022-11-10 refactor: Increase performance in searching for source files
2022-11-10 refactor: Prevent make_src from searching for top module twice
2022-11-10 refactor: Rename reset_bitfile to distribute_bitfiles for readability
2022-11-10 refactor: Remove old make commands for project initialization
2022-11-10 feat: Reorder boards dir and add constraints with board .tcl files
    feat: Reorder boards dir and add constraints with board .tcl files
    feat: Reorder boards dir and add constraints with board .tcl files
2022-11-10 refactor: Remove redundant handoff files
    refactor: Remove redundant handoff files
2022-11-10 fix: Adapt changes to new simulator environment in makefiles
2022-11-10 refactor: Fix typos in make commands
    refactor: Fix typos in make commands
2022-11-10 feat: Refresh codebase and add board generator for mode locking two lasers
    feat: Refresh codebase and add board generator for mode locking two lasers
2022-11-10 feat: Enable loading new board files without 'make reset cmd
2022-11-10 refactor: Regenerate project environment with memristor project
    refactor: Regenerate project environment with memristor project
2022-11-10 refactor: Rename board tcl file top to reflect its purpose
    refactor: Rename board tcl file top to reflect its purpose
2022-11-10 feat: Add source files for memristor project
2022-11-10 fix: Remove unwanted file from win11 installers
2022-11-10 fix: Adapt project sim tools to the new simulator environment
2022-11-10 fix: Correct gitignore logic for directory boards
    fix: Correct gitignore logic for directory boards
2022-11-10 feat: Use nano editor for rebase
2022-11-10 refactor: Test gitignore
    refactor: Test gitignore
    refactor: Test gitignore
    refactor: Test gitignore
    refactor: Test gitignore
    refactor: Test gitignore
    refactor: Test gitignore
2022-11-10 refactor: Remove redundant handoff files
2022-11-10 refactor: Remove redundant git make commands
2022-11-10 fix: Correct logic for pushing changes in boards to template repo
    fix: Correct logic for pushing changes in boards to template repo
    fix: Correct logic for pushing changes in boards to template repo
    fix: Correct logic for pushing changes in boards to template repo
    fix: Correct logic for pushing changes in boards to template repo
    fix: Correct logic for pushing changes in boards to template repo
    fix: Correct logic for pushing changes in boards to template repo
2022-11-10 fix: Correct duplicated commits
2022-11-10 fix: Change the Git dir in automated git clone script
2022-11-15 feat: Support arbitrary board parts to build board designs
2022-11-16 feat: Update XDC files for multiple devices
2022-11-17 refactor: Improve code for readability
2022-11-18 fix: Adapt code for memristor project target platform
2022-11-23 fix: Refresh code of the memristor project for multiple platforms
2022-12-10 fix: Refresh repository after upgrading software
2022-12-12 fix: Refresh repository after upgrading packages
2023-03-04 doc: Add documentation for board directory
2023-03-04 doc: Make changes related to sim documentation
2023-03-04 doc: Add documentation for tcl directory
2023-03-04 fix: Remove redundant brackets
2023-03-04 doc: Add documentation for alu_gflow
2023-03-05 feat: Add PCB layouts to the repo
2023-03-05 fix: Delete backups from XEM8350 pcb
2023-03-05 doc: Add documentation for fsm_gflow
2023-09-28 feat: Support gflow protocol for 8 qubits
2023-09-29 refactor: Restructure system build flow
2023-09-30 feat: Top_gflow.vhd to support 8 qubit operation
2023-10-03 fix: Implement bottom-up compilation for ModelSim
2023-11-04 refactor: Restructure codebase for a better user-friendly environment control
2023-11-04 feat: Add Opal Kelly IP Cores to the IP directory
2024-01-30 feat: Implement essentials
2024-05-22 feat: Allow py_gui display arbitrary number of generics
2024-05-23 fix: Correct the order of commands for compiling sim libraries
2024-06-02 feat: Add variable delay for PCD control signal
2024-06-10 refactor: Optimise for higher operating frequencies
2024-06-11 fix: Reconnect readout and perform optimisations on 312.5 MHz clock
2024-06-15 feat: Implement tools to allow 600 MHz acquisition
2024-06-17 refactor: Replace clocking wizard with custom clock generator
2024-06-21 refactor: Perform delay analysis and optimisations
2024-06-22 feat: Add module for transferring counter value over clock boundaries
2024-06-29 refactor: Change Pinout Plan for FMC-HPC-BRK for a high performance
2024-07-02 refactor: Replace cumbersome ok_usb_32b_fifo_ctrl with csv_readout readout module
2024-07-03 fix: Adapt RX C++ readout to added csv_readout TX VHDL module
2024-07-04 refactor: Update constraints for successful timing closure
2024-07-04 fix: Clean .log files via make reset
2024-07-04 feat: Append readout signals timestamps in csv files
2024-07-04 refactor: Include readout data sampling timestamps to csv headers
2024-07-07 feat: Add CLI arguments support in csv_readout c++ files
2024-07-07 fix: Add reset for correct FIFO readout operation
2024-07-08 refactor: Implement and read mode bits from fsm_gflow timestamp counter
2024-07-09 feat: Implement LFSR-based input emulation with dynamic clock phase shifting for high precision
2024-07-11 fix: Correct integer-to-real conversion to operate with trailing zeros
2024-07-11 feat: Build designs via loop or enumeration in make
2024-07-14 feat: Allow to launch csv_readout executable from main Makefile
2024-07-16 feat: Implement 1x incremental place & route before bitgen for timing closure
2024-07-18 feat: Implement bitfile loader for xem7350 OK FPGA with artifact version switches
2024-07-20 refactor: Add build hash and generic parameters into csv database
2024-07-20 refactor: Program FPGA through specific design md5 hash in opalkelly_bitloader.py
2024-07-21 refactor: Update artifact generation organisation and variable names for readability
2024-07-21 refactor: Prototyping gupdate_ownrepo make command
2024-07-21 fix: gupdate_ownrepo now evaluates zero string length in git diff output
2024-07-21 refactor: Git update local changes from currently checked out repo only
2024-07-21 refactor: Copy opalkelly_bitloader.py to outputs dir in make get_vivado_outputs
2024-07-22 refactor: Change outputs dir path to project root directory
2024-07-22 refactor: Probe photon 1H and photon 1V signals after acquisition
2024-12-04 feat: Tested two qubit feedforward
2024-12-18 refactor: Recentre coincidence window & bugfix
2024-12-20 feat: Test top_flowambiguity
2025-01-08 feat: Preliminary gflow duty cycle control prototype
2025-01-21 feat: Gflow protocol environment ready for testing
2025-02-09 bugfix: Revert changes in char* to std:string conversion
2025-02-09 bugfix: Fixes in csv_readout and gflow control
2025-04-16 fix: Correct pthon and cpp interface
